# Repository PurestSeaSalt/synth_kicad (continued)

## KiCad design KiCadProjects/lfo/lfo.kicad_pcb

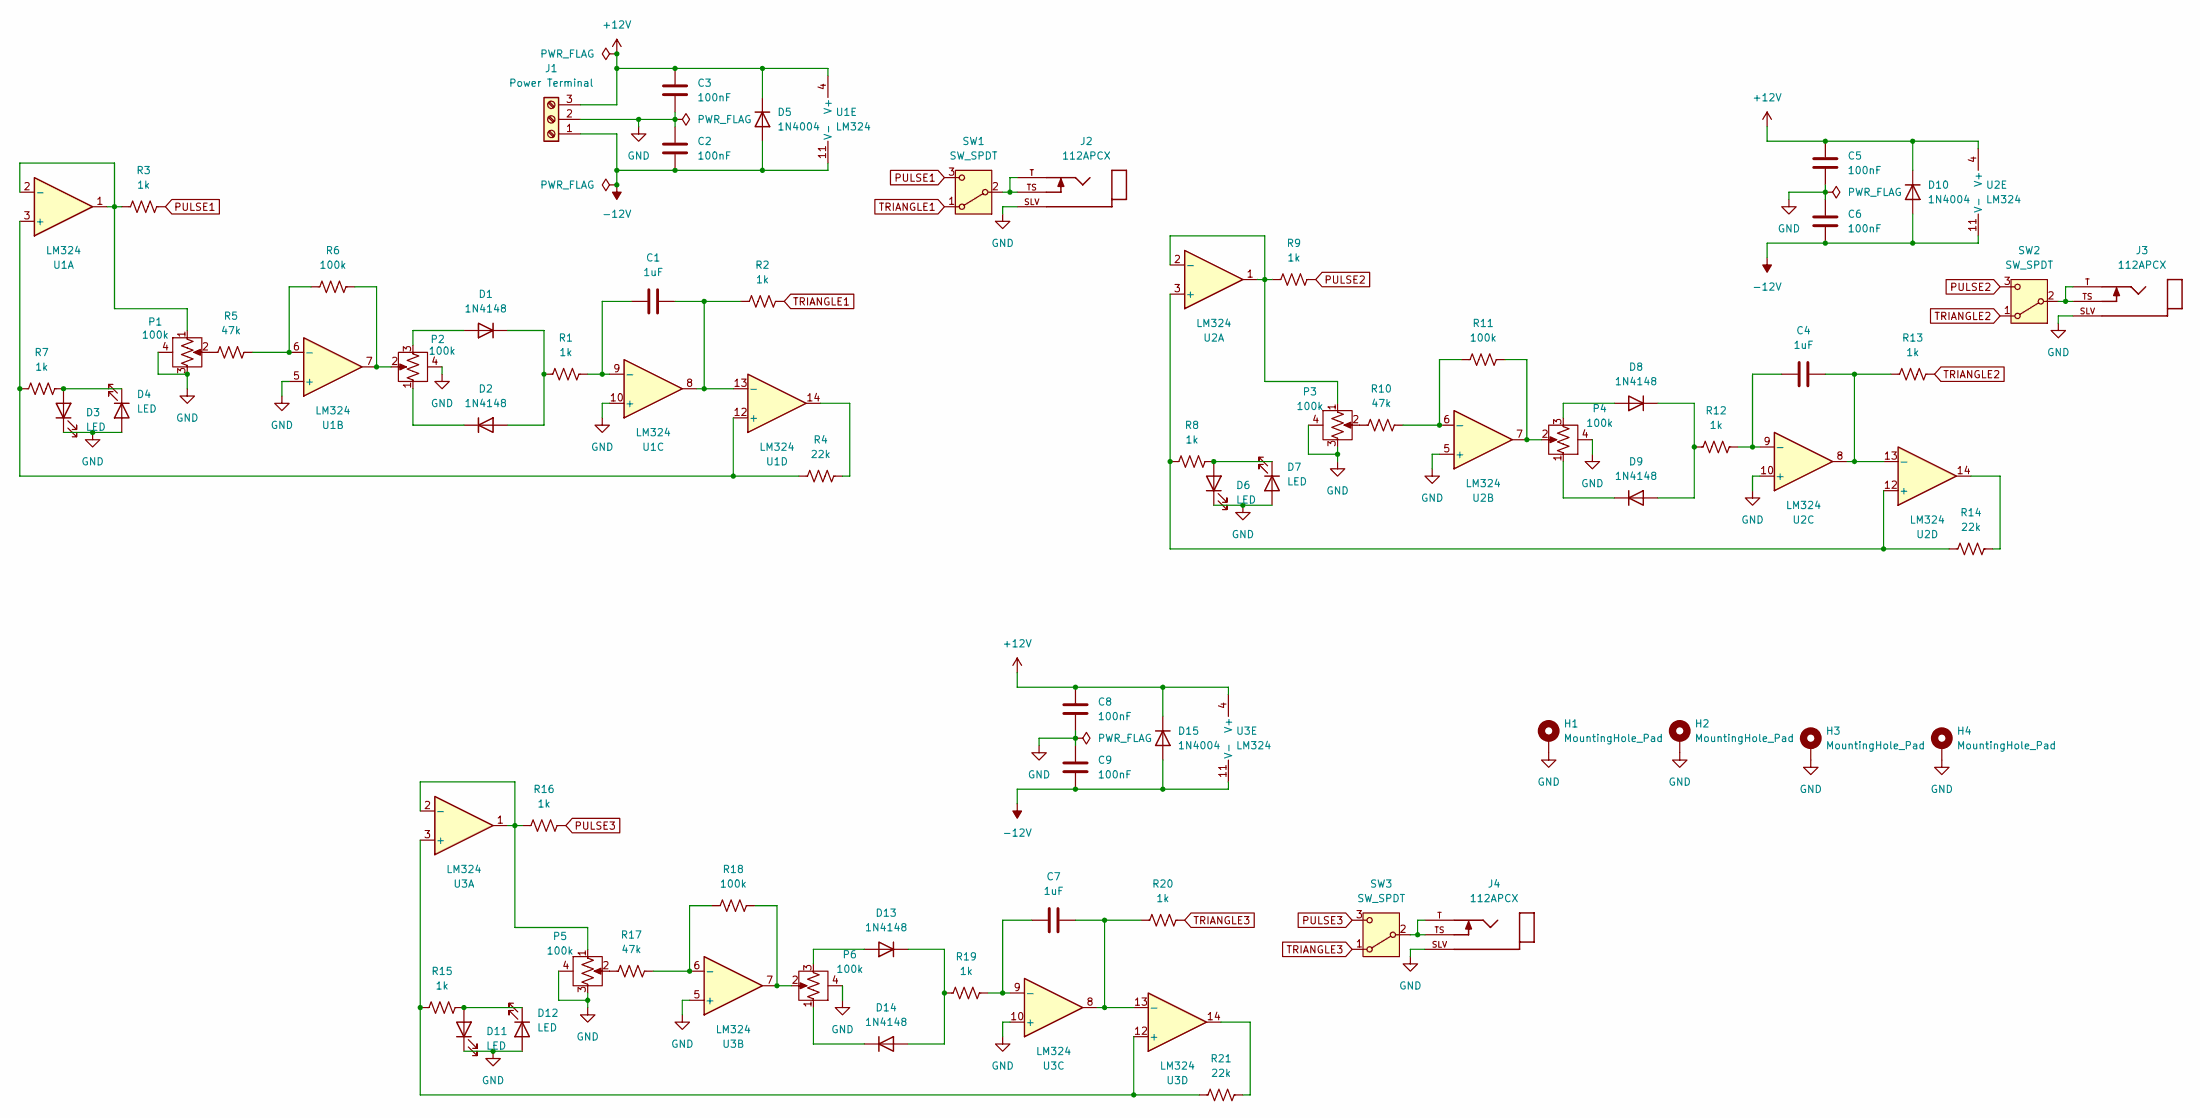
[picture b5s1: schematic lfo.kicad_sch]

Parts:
C1, C4, C7: 1uF; C_Disc_D5.0mm_W2.5mm_P5.00mm; Part No. 399-9886-1-ND
C2, C3, C5, C6, C8, C9: 100nF; C_Disc_D5.0mm_W2.5mm_P5.00mm; Part No. 399-4148-ND
D1, D2, D8, D9, D13, D14: 1N4148; D_DO-35_SOD27_P7.62mm_Horizontal; Part No. 1N4148FS-ND
D3, D4, D6, D7, D11, D12: LED; LED_D5.0mm; Part No. 732-5016-ND
D5, D10, D15: 1N4004; D_DO-41_SOD81_P10.16mm_Horizontal; Part No. 4878-1N4004CT-ND
H1, H2, H3, H4: MountingHole_Pad; MountingHole_4.3mm_M4_Pad
J1: Power Terminal; TerminalBlock_TE_282834-3_1x03_P2.54mm_Horizontal; Part No. A98334-ND
J2, J3, J4: 112APCX; SWITCHCRAFT_112APCX; PARTREV A
P1, P2, P3, P4, P5, P6: 100k; pot; Part No. PDB12-M4251-104BF-ND
R1, R2, R3, R7, R8, R9, R12, R13, R15, R16, R19, R20: 1k; R_Axial_DIN0207_L6.3mm_D2.5mm_P7.62mm_Horizontal; Part No. CF12JT1K00CT-ND
R4, R14, R21: 22k; R_Axial_DIN0207_L6.3mm_D2.5mm_P7.62mm_Horizontal; Part No. CF12JT22K0TR-ND
R5, R10, R17: 47k; R_Axial_DIN0207_L6.3mm_D2.5mm_P7.62mm_Horizontal; Part No. CF12JT47K0TR-ND
R6, R11, R18: 100k; R_Axial_DIN0207_L6.3mm_D2.5mm_P7.62mm_Horizontal; Part No. CF12JT100KTR-ND
SW1, SW2, SW3: SW_SPDT; SW_100SP1T1B4M2QE; Part No. EG2355-ND
U1, U2, U3: LM324; DIP-14_W7.62mm_Socket; Part No. 296-9542-5-ND

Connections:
+12V: C3.1, C5.1, C8.1, D5.1 (K), D10.1 (K), D15.1 (K), J1.3, U1.4 (V+), U2.4 (V+), U3.4 (V+)
-12V: C2.2, C6.2, C9.2, D5.2 (A), D10.2 (A), D15.2 (A), J1.1, U1.11 (V-), U2.11 (V-), U3.11 (V-)
GND: C2.1, C3.2, C5.2, C6.1, C8.2, C9.1, D3.1 (K), D4.2 (A), D6.1 (K), D7.2 (A), D11.1 (K), D12.2 (A), H1.1, H2.1, H3.1, H4.1, J1.2, J2.SLV, J3.SLV, J4.SLV, P1.3, P1.4, P2.4, P3.3, P3.4, P4.4, P5.3, P5.4, P6.4, U1.5 (+), U1.10 (+), U2.5 (+), U2.10 (+), U3.5 (+), U3.10 (+)
unnamed: D1.2 (A), P2.3
unnamed: D1.1 (K), D2.2 (A), R1.1
unnamed: D2.1 (K), P2.1
unnamed: D3.2 (A), D4.1 (K), R7.1
unnamed: D6.2 (A), D7.1 (K), R8.1
unnamed: D8.2 (A), P4.3
unnamed: D8.1 (K), D9.2 (A), R12.1
unnamed: D9.1 (K), P4.1
unnamed: D11.2 (A), D12.1 (K), R15.1
unnamed: D13.2 (A), P6.3
unnamed: D13.1 (K), D14.2 (A), R19.1
unnamed: D14.1 (K), P6.1
unnamed: P1.2, R5.1
unnamed: P2.2, R6.2, U1.7
unnamed: P3.2, R10.1
unnamed: P4.2, R11.2, U2.7
unnamed: P5.2, R17.1
unnamed: P6.2, R18.2, U3.7
unnamed: R4.2, U1.14
unnamed: R14.2, U2.14
unnamed: R21.2, U3.14
unnamed: J2.T, J2.TS, SW1.2 (B)
unnamed: J3.T, J3.TS, SW2.2 (B)
unnamed: J4.T, J4.TS, SW3.2 (B)
unnamed: R4.1, R7.2, U1.3 (+), U1.12 (+)
unnamed: P1.1, R3.1, U1.1, U1.2 (-)
unnamed: R5.2, R6.1, U1.6 (-)
unnamed: C1.1, R1.2, U1.9 (-)
unnamed: C1.2, R2.1, U1.8, U1.13 (-)
unnamed: R8.2, R14.1, U2.3 (+), U2.12 (+)
unnamed: P3.1, R9.1, U2.1, U2.2 (-)
unnamed: R10.2, R11.1, U2.6 (-)
unnamed: C4.1, R12.2, U2.9 (-)
unnamed: C4.2, R13.1, U2.8, U2.13 (-)
unnamed: R15.2, R21.1, U3.3 (+), U3.12 (+)
unnamed: P5.1, R16.1, U3.1, U3.2 (-)
unnamed: R17.2, R18.1, U3.6 (-)
unnamed: C7.1, R19.2, U3.9 (-)
unnamed: C7.2, R20.1, U3.8, U3.13 (-)
PULSE1: R3.2, SW1.3 (C)
PULSE2: R9.2, SW2.3 (C)
PULSE3: R16.2, SW3.3 (C)
TRIANGLE1: R2.2, SW1.1 (A)
TRIANGLE2: R13.2, SW2.1 (A)
TRIANGLE3: R20.2, SW3.1 (A)

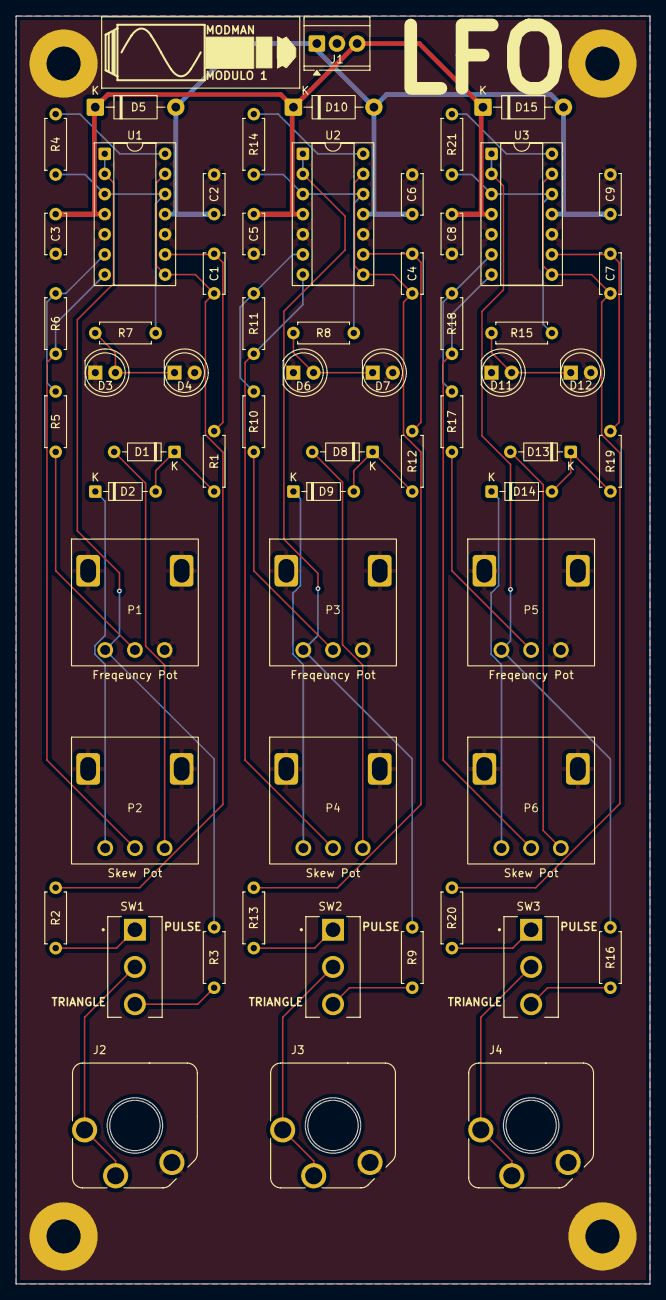
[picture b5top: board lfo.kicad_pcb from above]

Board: 2 copper layers, 80.0 x 160.0 mm, 65 parts (0 on the bottom side), 48 nets.

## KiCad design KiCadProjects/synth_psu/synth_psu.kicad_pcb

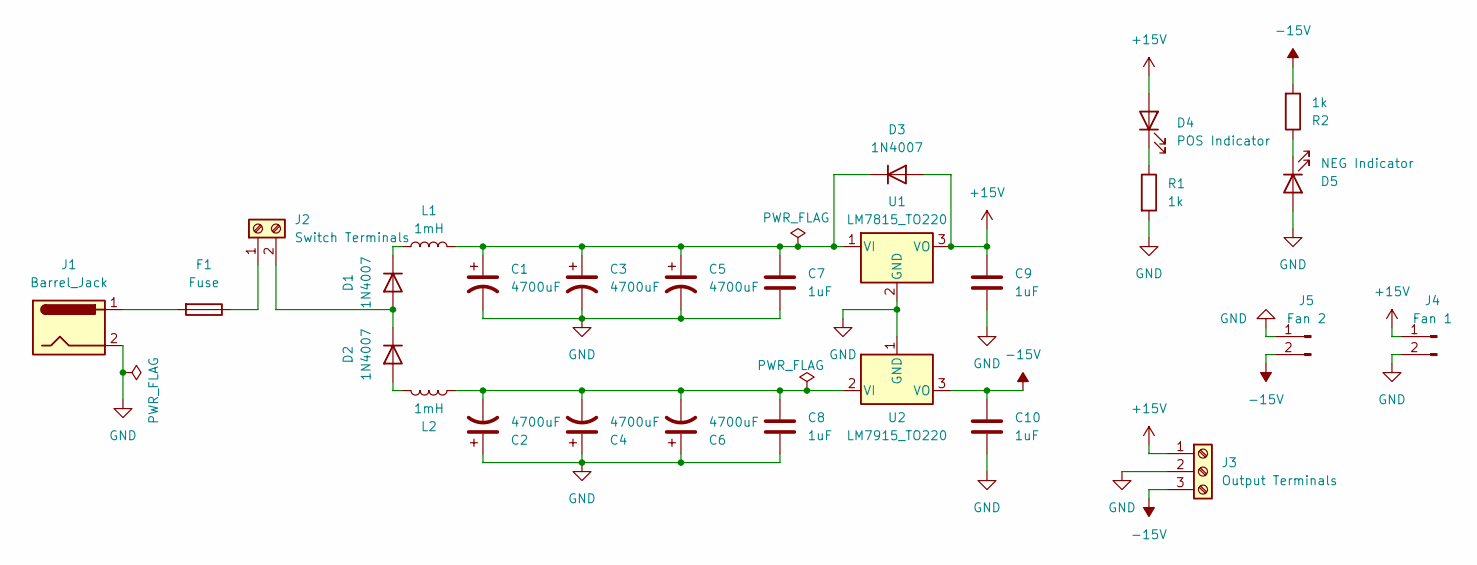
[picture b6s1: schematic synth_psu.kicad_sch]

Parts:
C1, C2, C3, C4, C5, C6: 4700uF; CP_Radial_D18.0mm_P7.50mm; Part No. 1189-1397-ND
C7, C8, C9, C10: 1uF; C_Disc_D5.0mm_W2.5mm_P5.00mm; Part No. 399-9886-1-ND
D1, D2, D3: 1N4007; D_DO-41_SOD81_P10.16mm_Horizontal; Part No. 4878-1N4007CT-ND
D4: POS Indicator; LED_D5.0mm; Part No. 732-5016-ND
D5: NEG Indicator; LED_D5.0mm; Part No. 732-5016-ND
F1: Fuse; Fuseholder_Clip-5x20mm_Littelfuse_100_Inline_P20.50x4.60mm_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; Part No. F6094-ND
J1: Barrel_Jack; BarrelJack_Horizontal
J2: Switch Terminals; TerminalBlock_TE_282834-2_1x02_P2.54mm_Horizontal; Part No. A98333-ND
J3: Output Terminals; TerminalBlock_TE_282834-3_1x03_P2.54mm_Horizontal; Part No. A98334-ND
J4: Fan 1; PinHeader_1x02_P2.54mm_Vertical; Part No. 952-2262-ND
J5: Fan 2; PinHeader_1x02_P2.54mm_Vertical; Part No. 952-2262-ND
L1, L2: 1mH; L_Toroid_Vertical_L21.6mm_W11.4mm_P7.62mm_Pulse_KM-3; Part No. M8863-ND
R1, R2: 1k; R_Axial_DIN0207_L6.3mm_D2.5mm_P7.62mm_Horizontal; Part No. CF12JT1K00CT-ND
U1: LM7815_TO220; TO-220-3_Vertical; Part No. 296-44418-5-ND
U2: LM7915_TO220; TO-220-3_Vertical; Part No. LM7915CT/NOPB-ND

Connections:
+15V: C9.1, D3.2 (A), D4.2 (A), J3.1, J4.1, U1.3 (VO)
-15V: C10.1, J3.3, J5.2, R2.2, U2.3 (VO)
GND: C1.2, C2.1, C3.2, C4.1, C5.2, C6.1, C7.2, C8.2, C9.2, C10.2, D5.2 (A), J1.2, J3.2, J4.2, J5.1, R1.2, U1.2 (GND), U2.1 (GND)
unnamed: D1.2 (A), D2.1 (K), J2.2
unnamed: D1.1 (K), L1.1
unnamed: D2.2 (A), L2.1
unnamed: C1.1, C3.1, C5.1, C7.1, D3.1 (K), L1.2, U1.1 (VI)
unnamed: D4.1 (K), R1.1
unnamed: D5.1 (K), R2.1
unnamed: F1.2, J1.1
unnamed: F1.1, J2.1
unnamed: C2.2, C4.2, C6.2, C8.1, L2.2, U2.2 (VI)

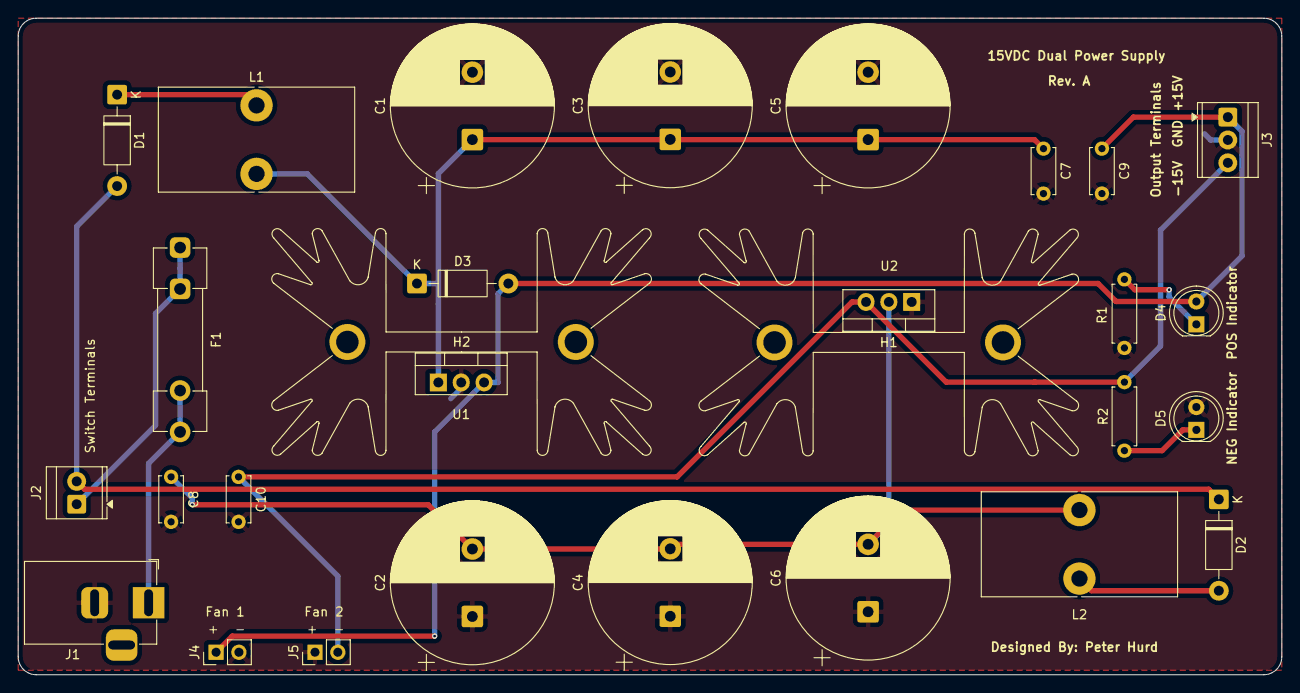
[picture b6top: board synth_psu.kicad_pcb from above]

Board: 2 copper layers, 140.5 x 73.0 mm, 29 parts (0 on the bottom side), 12 nets.

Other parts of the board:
H1, H2: Heatsink_Fischer_SK129-STS_42x25mm_2xDrill2.5mm

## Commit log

2025-06-28 add kibot scripts and projects
2025-06-28 remove old projects
2025-06-30 add vco project, add templates for action
2025-06-30 now add template
2025-06-30 actually add scripts this time
2025-06-30 update power schematic
2025-07-09 Add kibot?
2025-07-09 update to kicad 9
2025-08-13 updating github
2025-09-15 vco updates
2025-10-22 added vco top and bottom
2025-12-14 updates to temp circuit
2025-12-20 finish evm board
2026-04-02 temp sense rev 2
2026-06-05 Update ADS1115 Dev board
